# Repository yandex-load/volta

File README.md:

Yandex Volta is a framework for mobile performance and energy efficiency analysis.

[Telegram](https://t.me/joinchat/AAAAAAvBER7vU-672v1jbw) chat

**Table of Contents**

   * [Links](#links)
   * [What do you need](#what-do-you-need)
   * [Usage](#usage)
   * [Architecture](#architecture)
   * [Volta components](#volta-components)
   * [Using Volta](#using-volta)
      * [Command-line entry-point volta](#command-line-entry-point-volta)
      * [Core as module](#core-as-module)
      * [Data Providers](#data-providers)
         * [VoltaBox module](#voltabox-module)
         * [Phone module](#phone-module)
            * [Phone module - Android](#phone-module---android)
            * [Phone module - iPhone](#phone-module---iphone)
      * [Data Mappers](#data-mappers)
         * [Events module - Router](#events-module---router)
      * [Data Listeners](#data-listeners)
         * [Sync module - SyncFinder](#sync-module---syncfinder)
            * [Report module - FileListener](#report-module---filelistener)
            * [Uploader module - DataUploader](#uploader-module---datauploader)
      * [API](#api)
         * [HTTP API](#http-api)
   * [Questions](#questions)

# Links
A [mobile performance testing](https://www.youtube.com/watch?v=zcTG2PzXD3s) talk by Alexey Lavrenuke (in Russian).
An [article](https://habrahabr.ru/company/yandex/blog/311046/) about the device (in Russian).

# What do you need
* **A Volta Box**. Volta Box is an arduino-based current meter and power source for your mobile device. We will provide schematics after a while. Contact us if you want to get explanation right away.
* An **instrumented** mobile device. You need to extract a battery from your mobile device and connect **Volta Box** instead.
* If you want to control your device with **adb** while running your tests, you also need a current-limiting USB cable. Currently, we use FET to make those (google "FET current limiter").

# Usage
Install with ```pip install volta```, connect your device, run ```volta```.

# Architecture

[yEd scheme](/docs/architecture.graphml)

# Volta components
There are different types of Volta modules

[Core](volta/core/core.py) - core module, configures test life cycle and test pipeline.
Creates, configures and controls other modules.

**Data Providers**
* [VoltaBox](volta/providers/boxes/) - module for different types of Volta Boxes.
* [Phone](volta/providers/phones/) - module for different types of phones. Android and iPhone supported.

**Data Mappers**
* [Events](volta/mappers/events/) - phone logs parser module.

**Data Listeners**
* [Sync](volta/listeners/sync/) - cross-corellation sync module, syncs volta logs to phone logs.
* [Uploader](volta/listeners/uploader/) - data uploader module (e.g. to Overload).
* [Report](volta/listeners/report/) - file write module.

# Using Volta

## Command-line entry-point `volta`
Use command-line entry-point `volta` with .yaml config
> `volta -c config.yaml`

Sample yaml config for cli-wrapper:
```yaml
volta:
  enabled: true
  type: '500hz'
  source: '/dev/cu.wchusbserial1420'
phone:
  enabled: true
  type: 'android'
  source: '01e345da733a4764'
sync:
  enabled: true
  search_interval: 30
```
This config creates a test with **VoltaBox500Hz** at **/dev/cu.wchusbserial1420** and android phone id **01e345da733a4764**, then starts to collect and process data from VoltaBox and the phone.

To stop the test, press **Ctrl+C** or send **SIGTERM** signal to the process.

## Core as module
Also, if you want to control test execution or integrate Volta into your CI, you can use Core as python library.
Core validates config and reads parts with `enabled`: `True` option only.

Sample usage:
```python
from volta.core.core import Core

config = {
    'volta': {
        'enabled': True,
        'source': '/dev/cu.wchusbserial1420',
        'type': 'binary'
    },
    'phone': {
        'enabled': True,
        'source': '01e345da733a4764',
        'type': 'android',
    },
   'sync': {
       'enabled': True,
       'search_interval': 30
    },
    'uploader':{
        'enabled': True,
        'task': 'LOAD-272'
    }
}

core = Core(config)
try:
    core.configure()
    core.start_test()
except KeyboardInterrupt:
    core.end_test()
finally:
    core.post_process()
```

## Data Providers
### VoltaBox module

If you want more flexibility using Volta components, you can use provided Volta modules (or write you own) as python classes.

Available configuration options:
* **source** (mandatory) - path to volta box device
* **sample_rate** - volta box sample rate, depends on software and which type of volta box you use. Default differs for each type of VoltaBox
* **chop_ratio** - chop ratio for incoming data, describes the way how pandas.DataFrames w/ data will be created. Default 1
* **baud_rate** - baud rate for VoltaBox. Default differs for each VoltaBox class.
* **grab_timeout** - timeout for data read from VoltaBox. Default 1

Sample usage:
```python
from volta.providers.boxes.box_binary import VoltaBoxBinary
from volta.core.config.dynamic_options import DYNAMIC_OPTIONS
from netort.validated_config import ValidatedConfig as VoltaConfig
import queue
import time

config_dict = {
    'volta': {
        'source': '/dev/cu.wchusbserial1420',
        'type': 'binary'
    }
}
config = VoltaConfig(config_dict, DYNAMIC_OPTIONS, 'volta.core')
volta_box = VoltaBoxBinary(config) # VoltaBox class
q = queue.Queue()  # queue for results
volta_box.start_test(q)  # start acquiring data
time.sleep(5)  # do something (start autotests, do manual testing ...)
volta_box.end_test()  # stop acquiring data

# you can read pandas.DataFrames from results queue,
# data format: `['uts', 'value']`. Microseconds from test start and electrical currents value.
print(q.get_nowait())
```

### Phone module

We have modules for Android and iPhone. If you want to use some other type of device (e.g. Windows Phone), you can write your own phone module.

#### Phone module - Android

Works with android phones. Reads/parses system logs (`adb logcat`), starts lightning app for synchronization, installs/starts/runs tests on device.

Available configuration options:
* **source** (mandatory) - android device id
* **lightning** - path to lightning application (used for synchronization)
* **lightning_class** - lightning application class (how to run the app)
* **test_apps** - list of apps that will be installed to device for test
    * may be an url, e.g. 'http://myhost.tld/path/to/file'
    * may be a path to file, e.g. '/home/users/netort/path/to/file.apk'
* **test_class** - app class for run_test() stage
* **test_package** - app package for run_test() stage
* **test_runner** - app runner for run_test() stage

Sample usage:
```python
from volta.providers.phones.android import AndroidPhone
from volta.core.config.dynamic_options import DYNAMIC_OPTIONS
from netort.validated_config import ValidatedConfig as VoltaConfig
import queue
import time
import logging

config_dict = {
    'phone': {
        'source': '01e345da733a4764',
        'type': 'android',
        'test_apps': [
            'http://hostname.tld/path/to/first/apk1.apk',
            'http://hostname.tld/path/to/second/apk2.apk',
        ],
        'test_class': 'ru.yandex.test.highload.Tests',
        'test_package': 'ru.yandex.mobile.test',
        'test_runner': 'android.support.test.runner.AndroidJUnitRunner'
    }
}
config = VoltaConfig(config_dict, DYNAMIC_OPTIONS, 'volta.core')

phone = AndroidPhone(config)  # create Phone class
q = queue.Queue()  # create python queue for results
phone.prepare()  # prepare phone for test - clean logs, install test apps and install volta's `lightning` app for synchronization
phone.start(q)  # start acquiring log messages
phone.run_test()  # run test app, specified in config
time.sleep(5)  # do something ...
phone.end()  # stop acquiring log messages

# you can read pandas.DataFrames from results queue,
# data format: `['sys_uts', 'message']`. Microseconds from first event in phone log and message.
print(q.get_nowait())
```

#### Phone module - iPhone

Works with iPhone. Reads/parses system logs (`cfgutil`). To use this module install [Apple Configurator 2](https://itunes.apple.com/us/app/apple-configurator-2/id1037126344?mt=12) and use Mac.

To install apps on iPhone and control them you need to use `Apple's Instruments`.

Everithing else is the same as for AndroidPhone class.

Available configuration options:
* **source** (mandatory) - Apple device ECID. Run `/Applications/Apple\ Configurator\ 2.app/Contents/MacOS/cfgutil list` for getting ECID.
* **util** - path to Apple Configurator 2. Default: `/Applications/Apple\ Configurator\ 2.app/Contents/MacOS/`

Sample usage:
```python
from volta.providers.phones.iphone import iPhone
from netort.validated_config import ValidatedConfig as VoltaConfig
from volta.core.config.dynamic_options import DYNAMIC_OPTIONS

import queue

config_dict = {
    'phone': {
        'source': '0x6382910F98C26',
        'type': 'iphone',
    }
}
config = VoltaConfig(config_dict, DYNAMIC_OPTIONS, 'volta.core')
phone = iPhone(config)  # create Phone class
q = queue.Queue()  # create python queue for results
phone.prepare()  # prepare for test
phone.start(q)  # start phone log data acquiring
phone.end()  # stop phone log data acquiring
```

## Data Mappers

### Events module - Router

Once you get data from one of your phone modules, parse it with **EventsRouter**. It reads phone's results queue, parses messages, groups them by different types and sends them to listeners.

Also, applications can write any information you want into phone's system log to use later for debugging/better synchronization or mark some special events.

Available configuration options: None

Special messages format:
```
[volta] %nanotime% %type% %tag% %message%
```

Special message format sample:
```
[volta] 12345678 fragment TagFragment start
```

Currently we have those types of special messages supported by **EventsRouter**:
* **sync** - synchronization message, Sync module uses it for cross-correlation
* **event** - event message, you can write any information you need by your application on phone and send it to system log
* **fragment** - fragment message, used to mark fragments of events in your test
* **metric** - just a metric with float value instead of message.

Everything else (e.g. default phone system log messages) is grouped to **unknown** message type.

Sample usage:
```python
from volta.providers.phones.android import AndroidPhone
from volta.mappers.events.router import EventsRouter
from volta.listeners.report.report import FileListener
from volta.core.config.dynamic_options import DYNAMIC_OPTIONS
from netort.validated_config import ValidatedConfig as VoltaConfig

import queue
import time
import uuid

test_id = uuid.uuid4()  # some test id

config_dict = {
    'phone': {
        'source': '01e345da733a4764',
        'type': 'android',
    },
}
config = VoltaConfig(config_dict, DYNAMIC_OPTIONS, 'volta.core')
phone = AndroidPhone(config)  # create Phone instance
phone_q = queue.Queue()  # create python queue for results
phone.start(phone_q)  # start acquiring phone log messages

event_types = ['event', 'sync', 'fragment', 'metric', 'unknown'] # define event types
event_listeners = {key:[] for key in event_types} # create dict w/ empty list for each event type

event_fnames = {
    key:"{data}_{id}.data".format(
        data=key,
        id=test_id
    ) for key in event_types
}  # file name for each event type

# setup FileListener for each event type (at this sample we write each event type to its own file)
for type, fname in event_fnames.items():
    listener_config = {'fname': fname}
    f = FileListener(listener_config)
    event_listeners[type].append(f)

events_router = EventsRouter(phone_q, event_listeners)
events_router.start()  # start phone log messages processing and routing

time.sleep(10)
phone.end()  # stop acquiring phone log messages
time.sleep(5)
events_router.close()  # stop phone log messages processing and rouring

# in the end you will have files w/ events for each event type in current working directory
```

## Data Listeners
### Sync module - SyncFinder
Module for time synchronization. Calculates synchronization offsets for volta current measurements and phone's system log.
Uses fast Fourier transform convolution.

Available configuration options:
* **search_interval** -  sync search interval, in seconds from start. Default 30
* **sample_rate** - volta samplerate. Default 500

Sample usage:
```python
from volta.core.config.dynamic_options import DYNAMIC_OPTIONS
from volta.providers.boxes.box500hz import VoltaBox500Hz
from volta.providers.phones.android import AndroidPhone
from volta.mappers.events.router import EventsRouter
from volta.listeners.sync.sync import SyncFinder
from netort.data_processing import Tee
from netort.validated_config import ValidatedConfig as VoltaConfig

import queue
import time

# setup Volta and start
config_dict = {
    'volta': {
        'source': '/dev/cu.wchusbserial1420',
        'type': '500hz'
    },
    'phone': {
        'source': '01e345da733a4764',
        'type': 'android'
    },
    'sync': {
        'search_interval': 30
    },
}
config = VoltaConfig(config_dict, DYNAMIC_OPTIONS, 'volta.core')
volta_box = VoltaBox500Hz(config)  # create VoltaBox class
volta_q = queue.Queue()  # create python queue for volta results
volta_listeners = []  # create electrical current listeners list

# setup Phone and start
phone = AndroidPhone(config)  # create Phone class
phone_q = queue.Queue()  # create python queue for results

# setup EventsRouter
event_types = ['event', 'sync', 'fragment', 'metric', 'unknown']  # define event types
event_listeners = {key:[] for key in event_types}  # create dict w/ empty list for each event type
events_router = EventsRouter(phone_q, event_listeners)

# at the moment we have electrical currents queue and phone queue
sync_finder = SyncFinder(config)  # create SyncFinder class

# subscribe our SyncFinder to electrical current and sync events
volta_listeners.append(sync_finder)
event_listeners['sync'].append(sync_finder)

# now process electrical currents to listeners
# Tee drains the queue and send data to listeners
process_volta_data = Tee(
    volta_q,
    volta_listeners,
    'currents'
)

volta_box.start_test(volta_q)  # start volta_box data acquiring
process_volta_data.start()  # start volta_box data processing
phone.start(phone_q)  # start acquiring phone log messages
events_router.start()  # start phone logs processing and routing

# do some work... or maybe phone.run_test()
time.sleep(15)

volta_box.end_test()  # stop volta_box data acquiring
process_volta_data.close()  # stop volta_box data processing
phone.end()  # stop acquiring phone log messages
events_router.close()  # stop phone logs processing and routing

offsets = sync_finder.find_sync_points()
print(offsets)
# output format:
# sys_uts_offset is the phone's system uts to volta's uts offset
# log_uts_offset is the phone's logs custom events nanotime to volta's uts offset
# {'sys_uts_offset': -1005000, 'sync_sample': 0, 'log_uts_offset': 0}
```

#### Report module - FileListener
Saves data to a file.

Available configuration options:
* **fname** (mandatory) - Path to file.

Sample usage:
```python
from volta.providers.boxes.box500hz import VoltaBox500Hz
from volta.listeners.report.report import FileListener
from volta.core.config.dynamic_options import DYNAMIC_OPTIONS
from netort.data_processing import Tee
from netort.validated_config import ValidatedConfig as VoltaConfig
import queue
import time
import logging

config_dict = {
    'volta': {
        'source': '/dev/cu.wchusbserial1420',
        'type': '500hz'
    }
}
config = VoltaConfig(config_dict, DYNAMIC_OPTIONS, 'volta.core')
volta_box = VoltaBox500Hz(config)  # VoltaBox class
volta_q = queue.Queue()  # queue for results
volta_listeners = []  # empty list for listeners

# create FileListeners and subscribe it to volta
report_config = {'fname': 'current_output_filename'}
file_listener = FileListener(report_config)
volta_listeners.append(file_listener)

volta_data_process = Tee(volta_q, volta_listeners, 'currents')  # start volta data processing

volta_box.start_test(volta_q)  # start test and pass results queue
volta_data_process.start()
time.sleep(15) # do something (start autotests, do manual testing ...). I passed 5 seconds sleep as a placeholder.
volta_box.end_test()  # end test execution
volta_data_process.close()
```

#### Uploader module - DataUploader
Upload data. Currently supports only clickhouse TSV upload.

Available configuration options:
* **address** (mandatory) - Path to destination.
* **task** (mandatory) - You can specify task id manually.
* **test_id** - You can specify test id manually, otherwise it will be automatically generated (using uuid)

Sample yaml config section for uploader:
```yaml
uploader:
  enabled: true,
  address: 'https://lunapark.test.yandex-team.ru/api/volta'
  task: 'LOAD-272'
```

Sample usage:
```python
from volta.providers.boxes.box500hz import VoltaBox500Hz
from volta.listeners.uploader.uploader import DataUploader
from volta.core.config.dynamic_options import DYNAMIC_OPTIONS
from netort.data_processing import Tee
from netort.validated_config import ValidatedConfig as VoltaConfig
import queue
import time
import logging

config_dict = {
    'volta': {
        'source': '/dev/cu.wchusbserial1420',
        'type': '500hz'
    },
    'uploader': {
        'task': 'LOAD-272'
    }
}
config = VoltaConfig(config_dict, DYNAMIC_OPTIONS, 'volta.core')
volta_box = VoltaBox500Hz(config)  # VoltaBox class
volta_q = queue.Queue()  # queue for results
volta_listeners = []  # emptry list for listeners

# create DataUploader and subscribe it to volta_box
uploader = DataUploader(config)
volta_listeners.append(uploader)

volta_data_process = Tee(volta_q, volta_listeners, 'currents')  # start volta data processing

volta_box.start_test(volta_q)  # start test and pass results queue
volta_data_process.start()
time.sleep(15) # do something (start autotests, do manual testing ...). I passed 5 seconds sleep as a placeholder.
volta_box.end_test()  # end test execution
volta_data_process.close()
```

## API
### HTTP API (concurrent tests, improved statuses)
Allows to start and stop test via HTTP interface.

Entry point: `volta-api`

Simply put config into a POST body.

Start test sample:
```bash
curl 'http://localhost:9998/api/v1/start/' --data 'config={"volta":{"source":"/dev/cu.wchusbserial1420","type":"500hz","enabled":True}, "uploader": {"enabled": True, "task":"LOAD-272"},"phone":{"source":"1f434a75","type":"android","enabled":True}}' -v
```

Stop test sample:
```bash
curl 'http://localhost:9998/api/v1/stop?session=20170801180806_0000000000'
```

Check test status:
```bash
curl 'http://localhost:9998/api/v1/status?session=20170801180806_0000000000'
```

### simple and mini HTTP API (no concurrent tests allowed)
Allows to start and stop test via HTTP interface.

Entry point: `volta-http`

Simply put config into a POST body.

Start test sample:
```bash
curl 'http://localhost:9998/api/v1/start/' --data 'config={"volta":{"source":"/dev/cu.wchusbserial1420","type":"500hz","enabled":True}}' -v
```

Stop test sample:
```bash
curl 'http://localhost:9998/api/v1/stop/' -XPOST -v
```

# Questions
Any questions to Alexey Lavrenuke <direvius@yandex-team.ru> OR [Telegram](https://t.me/joinchat/AAAAAAvBER7vU-672v1jbw) chat.

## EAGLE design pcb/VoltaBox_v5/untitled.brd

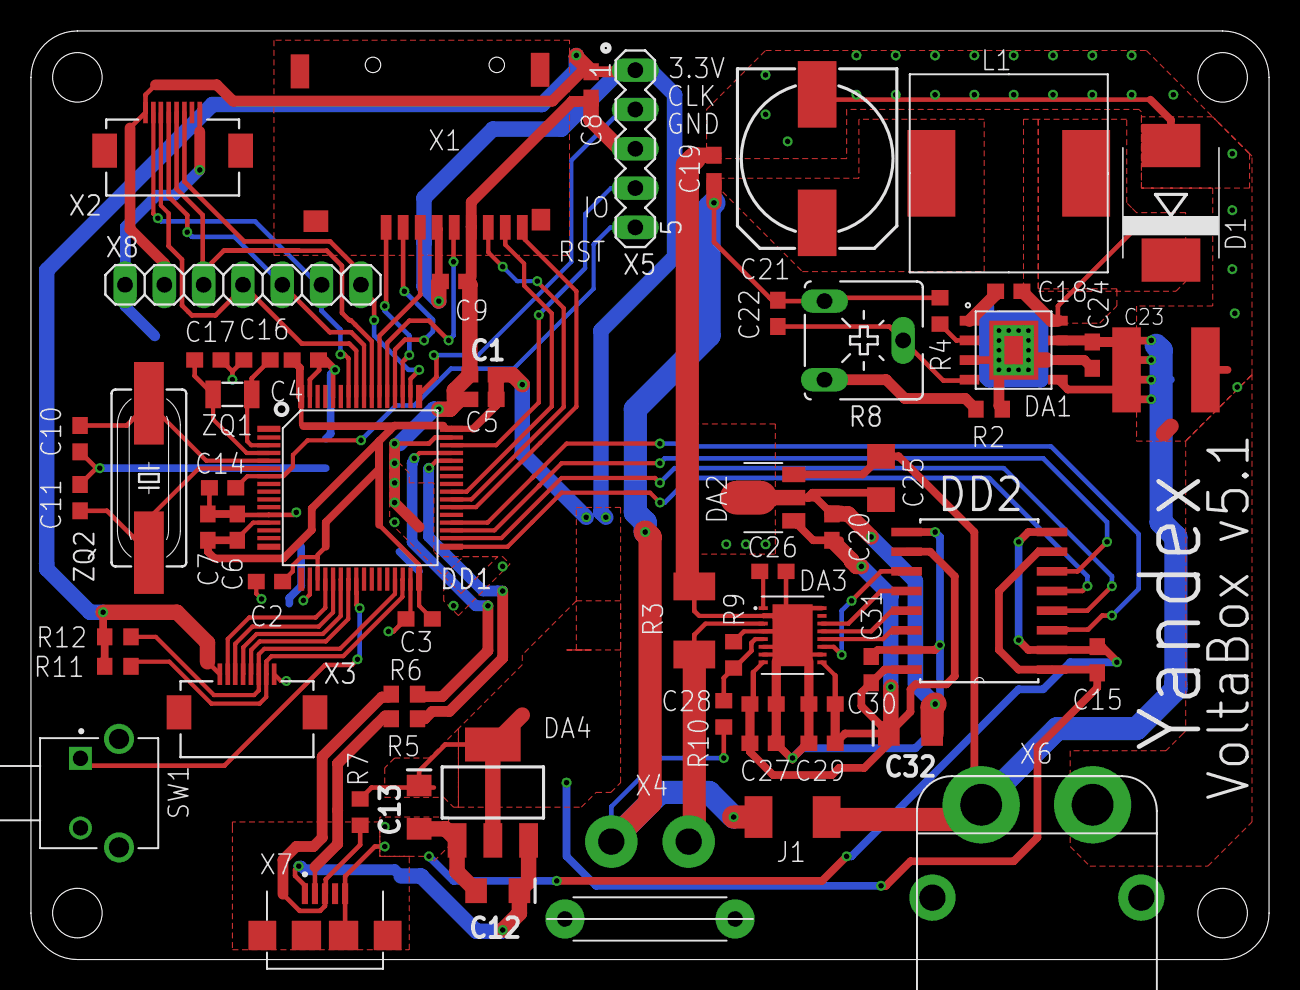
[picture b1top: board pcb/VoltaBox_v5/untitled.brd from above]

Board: 2 copper layers, 80.0 x 60.0 mm, 63 parts (0 on the bottom side), 53 nets.

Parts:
C1: 4.7uF; 0603
C2, C3, C4, C5, C14, C15, C18, C19, C20, C24, C28, C29, C31: 0.1u; C0603
C6, C8, C9, C26: 1u; C0603
C7: 10n; C0603
C10, C11, C16, C17: 15p; C0603
C12, C13, C32: 10uF; EIA3216
C21: 100u; 150CLZ-1014
C22: 150p; C0603
C23: 4.7u; C2220K
C25: 1u; C1206
C27, C30: 10p; C0603
D1: STPS5L60S; SMC
DA1: ST1S14; HSOP8
DA2: 78L05F; SOT89
DA3: LMP92064SD/NOPB; SON50P400X500X80-17N
DA4: SOT223
DD1: MCU-STM32F103RCT6(LQFP64); LQFP64-0.5-10X10MM
DD2: ADUM1401CRWZ; SO-16W
J1: 0; R2010
L1: B82477G4
R2, R10: 2.7K; R0603
R3: 0.025; R2010
R4: 47K; R0603
R5, R6: 22; R0603
R7: 1.5k; R0603
R8: 10k; CA6V
R9: 1.2K; R0603
R11, R12: 10k; R0603
SW1: FSMRA6JH; TE_FSMRA6JH
X1: 112J-TDAR-R(MICROSD); 112J-TDAR-R
X2, X3: 52892-0895; MOLEX_52892-0895
X4: XT30PW-F
X5: MA05-1
X6: XT60PW-M
X7: KLS1-233
X8: 1X07
ZQ1: 32768Hz; 3.2X1.5
ZQ2: 8MHz; HC49UP

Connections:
+3V3: C1.1, C2.1, C3.1, C4.1, C5.1, C6.1, C7.1, C8.1, C9.1, C13.+, C15.1, DA4.2, DA4.4, DD1.13, DD1.19, DD1.32, DD1.48, DD1.64, DD2.1, DD2.7, R7.2, R11.2, R12.2, X1.P$4, X2.1, X3.1, X5.1, X8.2
+4V: C19.1, C21.+, C22.2, J1.2, L1.P$2, R4.2, R8.A, R10.2, X4.P$2
+5V: C20.1, C27.1, C28.1, C29.1, C30.1, C31.1, C32.+, DA2.1, DA3.8, DA3.9, DD2.10, DD2.16
+12V: C23.1, C24.1, C25.1, DA1.5, DA1.7, DA2.3, J1.1, X6.P$2
ADC_MISO: DD1.35, DD2.6
ADC_MOSI: DD1.36, DD2.3
ADC_NSS: DD1.33, DD2.5
ADC_SCK: DD1.34, DD2.4
AGND: C19.2, C20.2, C21.-, C23.2, C24.2, C25.2, C26.2, C27.2, C28.2, C29.2, C30.2, C31.2, C32.-, D1.A, DA1.3, DA1.6, DA1.P$9, DA1.P$10, DA1.P$11, DA1.P$12, DA1.P$13, DA1.P$14, DA1.P$15, DA1.P$16, DA1.P$17, DA1.P$18, DA1.P$19, DA1.P$20, DA1.P$21, DA1.P$22, DA2.2, DA2.2@1, DA3.2, DA3.4, DA3.6, DA3.7, DA3.10, DA3.16, DA3.17, DD2.9, DD2.15, R2.1, R3.1, R9.1, X6.P$1
DMCU_N: DD1.44, R5.2
DMCU_P: DD1.45, R6.2
D_N: R5.1, X7.2
D_P: R6.1, R7.1, X7.3
GND: C1.2, C2.2, C3.2, C4.2, C5.2, C6.2, C7.2, C8.2, C9.2, C10.2, C11.2, C12.-, C13.-, C14.2, C15.2, C16.2, C17.2, DA4.1, DD1.12, DD1.18, DD1.31, DD1.47, DD1.60, DD1.63, DD2.2, DD2.8, SW1.2, SW1.S1, SW1.S2, X1.P$6, X1.P$10, X1.P$11, X1.P$12, X1.P$13, X2.8, X3.8, X5.3, X7.5, X7.SH4, X7.SH5, X7.SH6, X7.SH7, X8.1
unnamed: C10.1, DD1.5, ZQ2.1
unnamed: C11.1, DD1.6, ZQ2.2
unnamed: C26.1, DA3.1
unnamed: C18.1, DA1.1
unnamed: DA3.13, DD2.13
unnamed: DA3.14, DD2.12
unnamed: C17.1, DD1.4, ZQ1.2
unnamed: C16.1, DD1.3, ZQ1.1
unnamed: C18.2, D1.C, DA1.8, L1.P$1
unnamed: C22.1, DA1.4, R8.S
unnamed: DA3.12, DD2.14
unnamed: DA1.2, R4.1
unnamed: DD1.54, X1.P$3
unnamed: DD1.53, X1.P$5
unnamed: DD1.52, X1.P$2
unnamed: DD1.51, X1.P$1
unnamed: DD1.24, SW1.1
unnamed: DD1.40, X1.P$8
unnamed: DD1.39, X1.P$7
unnamed: R2.2, R8.E
unnamed: DA3.3, R3.2, X4.P$1
unnamed: DD1.30, R11.1, X3.7
unnamed: DA3.5, R9.2, R10.1
unnamed: DA3.11, DD2.11
unnamed: DD1.29, R12.1, X3.6
unnamed: DD1.23, X3.5
unnamed: DD1.22, X3.4
unnamed: DD1.21, X3.3
unnamed: DD1.20, X3.2
unnamed: DD1.38, X1.P$9
NRESET: C14.1, DD1.7, X5.5
OLED_CS: DD1.50, X2.6, X8.7
OLED_DC: DD1.58, X2.2, X8.6
OLED_MOSI: DD1.57, X2.3, X8.4
OLED_RS: DD1.56, X2.4, X8.5
OLED_SCK: DD1.55, X2.5, X8.3
SWCLK: DD1.49, X5.2
SWDIO: DD1.46, X5.4
VCC: C12.+, DA4.3, X7.1

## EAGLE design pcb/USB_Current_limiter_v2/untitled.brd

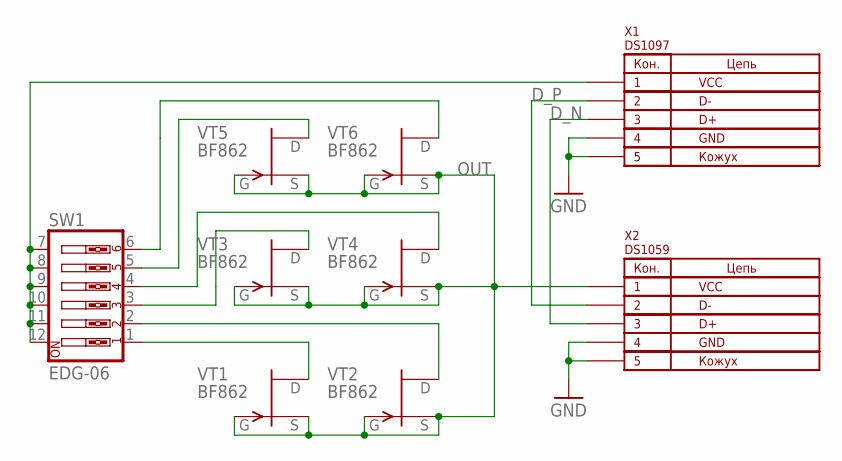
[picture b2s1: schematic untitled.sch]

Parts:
SW1: EDG-06
VT1, VT2, VT3, VT4, VT5, VT6: BF862; SOT23
X1: DS1097
X2: DS1059

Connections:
D_N: X1.P$2, X2.P$3
D_P: X1.P$3, X2.P$2
GND: X1.P$1, X1.P$5, X1.P$6, X2.P$4, X2.P$5, X2.P$6
unnamed: SW1.6, VT6.2 (D)
unnamed: SW1.7, SW1.8, SW1.9, SW1.10, SW1.11, SW1.12, X1.P$4
unnamed: SW1.5, VT5.2 (D)
unnamed: SW1.4, VT4.2 (D)
unnamed: SW1.3, VT3.2 (D)
unnamed: SW1.2, VT2.2 (D)
unnamed: SW1.1, VT1.2 (D)
OUT: VT1.1 (S), VT1.3 (G), VT2.1 (S), VT2.3 (G), VT3.1 (S), VT3.3 (G), VT4.1 (S), VT4.3 (G), VT5.1 (S), VT5.3 (G), VT6.1 (S), VT6.3 (G), X2.P$1

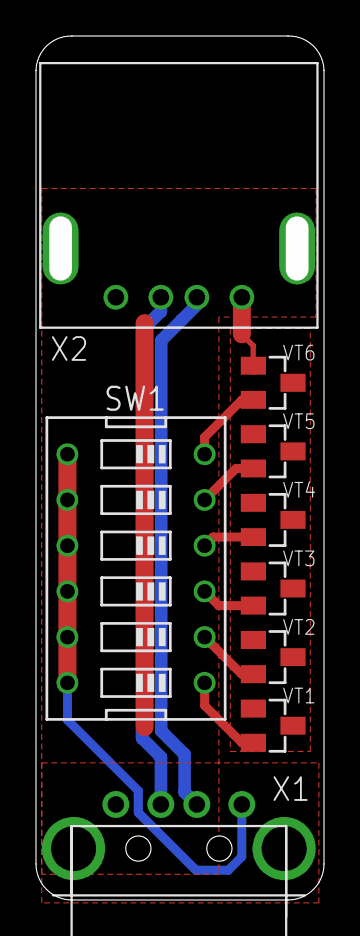
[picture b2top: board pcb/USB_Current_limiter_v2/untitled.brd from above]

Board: 2 copper layers, 16.0 x 48.0 mm, 9 parts (0 on the bottom side), 11 nets.

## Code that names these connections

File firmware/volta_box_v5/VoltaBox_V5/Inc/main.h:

/**
  ******************************************************************************
  * @file           : main.h
  * @brief          : Header for main.c file.
  *                   This file contains the common defines of the application.
  ******************************************************************************
  * This notice applies to any and all portions of this file
  * that are not between comment pairs USER CODE BEGIN and
  * USER CODE END. Other portions of this file, whether 
  * inserted by the user or by software development tools
  * are owned by their respective copyright owners.
  *
  * Copyright (c) 2018 STMicroelectronics International N.V. 
  * All rights reserved.
  *
  * Redistribution and use in source and binary forms, with or without 
  * modification, are permitted, provided that the following conditions are met:
  *
  * 1. Redistribution of source code must retain the above copyright notice, 
  *    this list of conditions and the following disclaimer.
  * 2. Redistributions in binary form must reproduce the above copyright notice,
  *    this list of conditions and the following disclaimer in the documentation
  *    and/or other materials provided with the distribution.
  * 3. Neither the name of STMicroelectronics nor the names of other 
  *    contributors to this software may be used to endorse or promote products 
  *    derived from this software without specific written permission.
  * 4. This software, including modifications and/or derivative works of this 
  *    software, must execute solely and exclusively on microcontroller or
  *    microprocessor devices manufactured by or for STMicroelectronics.
  * 5. Redistribution and use of this software other than as permitted under 
  *    this license is void and will automatically terminate your rights under 
  *    this license. 
  *
  * THIS SOFTWARE IS PROVIDED BY STMICROELECTRONICS AND CONTRIBUTORS "AS IS" 
  * AND ANY EXPRESS, IMPLIED OR STATUTORY WARRANTIES, INCLUDING, BUT NOT 
  * LIMITED TO, THE IMPLIED WARRANTIES OF MERCHANTABILITY, FITNESS FOR A 
  * PARTICULAR PURPOSE AND NON-INFRINGEMENT OF THIRD PARTY INTELLECTUAL PROPERTY
  * RIGHTS ARE DISCLAIMED TO THE FULLEST EXTENT PERMITTED BY LAW. IN NO EVENT 
  * SHALL STMICROELECTRONICS OR CONTRIBUTORS BE LIABLE FOR ANY DIRECT, INDIRECT,
  * INCIDENTAL, SPECIAL, EXEMPLARY, OR CONSEQUENTIAL DAMAGES (INCLUDING, BUT NOT
  * LIMITED TO, PROCUREMENT OF SUBSTITUTE GOODS OR SERVICES; LOSS OF USE, DATA, 
  * OR PROFITS; OR BUSINESS INTERRUPTION) HOWEVER CAUSED AND ON ANY THEORY OF 
  * LIABILITY, WHETHER IN CONTRACT, STRICT LIABILITY, OR TORT (INCLUDING 
  * NEGLIGENCE OR OTHERWISE) ARISING IN ANY WAY OUT OF THE USE OF THIS SOFTWARE,
  * EVEN IF ADVISED OF THE POSSIBILITY OF SUCH DAMAGE.
  *
  ******************************************************************************
  */

/* Define to prevent recursive inclusion -------------------------------------*/
#ifndef __MAIN_H__
#define __MAIN_H__

/* Includes ------------------------------------------------------------------*/

/* USER CODE BEGIN Includes */

/* USER CODE END Includes */

/* Private define ------------------------------------------------------------*/

#define SPI2_NSS_Pin GPIO_PIN_12
#define SPI2_NSS_GPIO_Port GPIOB
#define OLED_CS_Pin GPIO_PIN_15
#define OLED_CS_GPIO_Port GPIOA
#define OLED_SCK_Pin GPIO_PIN_3
#define OLED_SCK_GPIO_Port GPIOB
#define OLED_RS_Pin GPIO_PIN_4
#define OLED_RS_GPIO_Port GPIOB
#define OLED_MOSI_Pin GPIO_PIN_5
#define OLED_MOSI_GPIO_Port GPIOB
#define OLED_DC_Pin GPIO_PIN_6
#define OLED_DC_GPIO_Port GPIOB

/* ########################## Assert Selection ############################## */
/**
  * @brief Uncomment the line below to expanse the "assert_param" macro in the 
  *        HAL drivers code
  */
/* #define USE_FULL_ASSERT    1U */

/* USER CODE BEGIN Private defines */

/* USER CODE END Private defines */

#ifdef __cplusplus
 extern "C" {
#endif
void _Error_Handler(char *, int);

#define Error_Handler() _Error_Handler(__FILE__, __LINE__)
#ifdef __cplusplus
}
#endif

#endif /* __MAIN_H__ */

/************************ (C) COPYRIGHT STMicroelectronics *****END OF FILE****/

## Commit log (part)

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2017-02-16 reinit SD card every time
2017-02-17 fix led brightness
2017-02-17 verify=False everywhere
2017-02-17 version bump
2017-03-01 added task for console wiazrd
2017-03-01 task id for uploader, version bump
2017-03-01 fixes, raw data from sd-card uploader ignores meta info
2017-03-03 Added under construction css for wizard when test started
2017-03-05 added 1MHz and esp8266 firmwares
2017-03-06 20 seconds flashlight sync now
2017-03-06 added local graphs
2017-03-06 removed pngs
2017-03-06 local plots
2017-03-06 lunapark task checker added
2017-03-06 add test fragments parsing, need to complete uploading
2017-03-07 added exception failover if user forgot to connect the box
2017-03-07 bugfixes
2017-03-12 bugfix
2017-03-14 4digit display support added
2017-03-17 filter trash and fill w/ zeroes while grabbing plain-text data
2017-03-20 jobno dump, version bump
2017-03-21 interrupts handler
2017-03-21 added env variables, added log events and fragments cosmetics
2017-03-21 added operator login to wizard ui
2017-03-22 removed pyqt and version bump
2017-03-22 bugfix, rollback of fragments. falsestart
2017-03-22 ver bump
2017-03-23 made uploader more stable if events not found
2017-03-23 appropriate logic for operator detection
2017-03-27 VoltaBox refactoring init
2017-03-28 VoltaBox refactoring
2017-03-28 architecture image, cosmetics
2017-03-28 VoltaBox binary refactoring
2017-03-28 TimeChopper moved to util, odd serial read workaround added -> orphan byte superstar
2017-03-28 cosmetics
2017-03-30 appropriate end for reader, file import mode for binary
2017-04-03 added resource manager, refactored volta boxes to work w/ resource manager
2017-04-05 Phone interface, android blank step implementation
2017-04-05 moved lightning to Phones, added resource manager to android
2017-04-05 usage sample fix
2017-04-05 install lightning apk
2017-04-07 android phone refactoring, 10khz filereader to dataframe bugfix
2017-04-07 cleanup
2017-04-10 wizard fixes, no connection to lunapark
2017-04-10 ui fixes
2017-04-11 Phones->android refactoring
2017-04-11 phone.run_test added to core
2017-04-12 more human-friendly cosmetics patch for android
2017-04-12 ver bumpg
2017-04-12 type fix
2017-04-12 todo added to android phone
2017-04-12 meta.duration removed
2017-04-12 cosmetics, code cleanup
2017-04-13 Phones -> iPhone refactoring init
2017-04-13 iphone and android timestamps to datetime
2017-04-13 code cleanup
2017-04-17 eventshandler init
2017-04-17 more flexible data usage in eventsparser
2017-04-17 regexp fixes
2017-04-17 removed redundant ? in regexp
2017-04-18 added ts to volta dataframes
2017-04-18 daterange for volta currents
2017-04-18 time.time -> utc
2017-04-18 start_time from test start
2017-05-05 sync finder init
2017-05-05 removed junk
2017-05-15 everything moved to async/threads, FileListener init, Sync reworked, Tee init
2017-05-16 file listeners refactoring, added header to filelisteners, separate file listeners for each event types
2017-05-17 uploader init
2017-05-17 cli init, yaml config parser and sample
2017-05-18 json/yaml support, failover cli config added
2017-05-19 readme bugfix
2017-05-19 Added scheme png
2017-05-19 readme fix
2017-05-22 Listeners refactoring, added interfaces and docstrings
2017-05-22 docstrings for core
2017-05-22 docstring redesign, LogReader for Phone refactoring
2017-05-22 moved to develop
2017-05-22 PEP8 naming for modules
2017-05-23 bugfix for android volta.Phones -> phones
2017-05-23 postloader init
2017-05-23 gitignore mac junk removal
2017-05-23 moved Boxes according to PEP8 module naming
2017-05-23 PEP8 module naming
2017-05-23 cleanup, removed junk
2017-05-24 Update README.md
    lil fixies
2017-05-25 reorganization eventsrouter
2017-05-25 events router documentation
2017-05-25 Sync class documentation
2017-05-25 relative links to modules
2017-05-25 readme update
2017-05-25 FileListener documentation
2017-05-26 added datauploader sampe and documentation
2017-05-26 typo fix
2017-05-26 Table of Contents
2017-05-29 package reorganization - group by type
2017-05-29 modules reorganization - update, readme update
2017-05-29 ToC update
2017-05-30 add Volta image
2017-05-30 update photo
2017-05-30 uploader meta upload, config samples
2017-05-30 uploader meta create and update job
2017-05-30 readme samples update
2017-05-30 key_date added to start of test_id
2017-06-01 http api v1
2017-06-01 more flexible error handling for api
2017-06-01 Readme for http api
2017-06-07 ToC update, API documentation
2017-06-07 uploader config readme fix
2017-06-17 add telegram chat link
2017-06-19 add demo ipynb
2017-06-22 uploader bug fix, added logging for sync stage
2017-06-22 Sync w/ master
2017-06-26 added sample configs, nexus4 phone, additional logging
2017-06-27 remove exceptional logging
2017-06-28 eventsrouter bugfix if message is empty
2017-06-28 removed infinite loop for phone events processing
2017-06-29 added lunapark id
2017-07-04 hotfix if row.message in router is empty
2017-07-12 added deps versions
2017-07-12 slope and offset for binary box
2017-07-17 custom regexp support
2017-07-20 android below 5 class
2017-07-20 old android phones core support
2017-07-20 validation for configuration system, refactoring
2017-07-20 android old refactoring
2017-07-20 samples updated
2017-07-21 documentation update for validator
2017-07-21 documentation update
2017-07-24 improvements for tank android plugin
2017-07-24 added event_regexp for validation schema.yaml
2017-07-24 removed unplug_type=manual
2017-07-26 volta core config update
2017-07-26 volta get test id handler added
2017-07-26 jobno, api_jobno renamed
2017-07-27 current test info method
2017-07-31 new webserver for API
2017-07-31 added future to deps
2017-07-31 manager, webserver and worker for API
2017-07-31 added readme and samples
2017-07-31 common cleanup
2017-07-31 appropriate artifacts handling and initialization
2017-08-01 api improvements, phone code cleanup
2017-08-01 Readme update, cosmetics
2017-08-02 binary apk bugfix
2017-08-02 bugfix of binary apk distribution
2017-08-02 revert back apk from MANIFEST
2017-08-14 device_id for tests
2017-08-17 iphone config bugfix
2017-08-17 bugfix again, version bump
2017-08-18 fix router if dataframe is None
2017-08-23 add firmware for ads7816 based VoltaBox
2017-08-25 removed sleeps for start test
2017-08-29 volta w/external ads
2017-08-29 version
2017-09-04 iphone bugfix
2017-09-15 removed infinite loop from iphone
2017-10-02 pcb schemas added
2017-10-09 ratatoskr@ patch
2017-10-09 sleep till flashlight app ends its work
2017-10-12 cleanup apps VOLTA-238
2017-10-12 cleanup bufixes
2017-10-20 stm32+ads7816 firmware boilerplate
2017-10-31 events router exceptions: trying to be more stable to bad events
2017-11-02 bug fix for log_uts_offset
2017-11-23 volta box v4
2017-11-24 Require 'enabled' option for volta module
2017-11-24 bugfix for events processing
2017-11-28 tutorial update
2017-11-30 VoltaBox v4 PCB
2017-11-30 update pcb
2017-12-07 added note about ECID for iOS
2017-12-07 fix some bugs
2017-12-18 uploader async w/ threading. refactoring uploader listener
2017-12-18 chop ratio validation fixes
2017-12-18 added retry for uploader
2017-12-19 additional exception for jobno dump, cosmetics
2017-12-19 send chunk method
2017-12-19 more suitable warning message for retry
2017-12-19 added test info for volta API for uploader sender thread
2017-12-26 get-state failover
2017-12-26 Ver bump|
2017-12-28 new schematics
2018-01-11 fixed bugs for threads, uploader thread refactoring and reorganization
2018-01-16 restore orphan byte
2018-01-16 revert back regress id, added daemons for threading Drain/Tee
2018-01-16 events router improvements, additional logging for events router and uploader
2018-01-16 uploader and android phone test performer improvements
2018-01-17 sample swap configuration
2018-01-19 Regress -> component
2018-01-23 uploader should now correctly finish its work
2018-01-26 empty dataframes skip for uploader
2018-01-29 new logging system and management, volta log added to artifacts
2018-02-01 exceptions for uploader, create_job and update_job timeouts and connection errors catch
2018-02-01 ver bump, bugfix
2018-02-21 new pcb
2018-02-21 ran python-modernize
2018-02-22 moved common utils to netort
2018-03-05 hardcoded port removed for http api
2018-03-07 readme and setup update
2018-03-07 requirements update
2018-03-07 post-loader improvements
2018-03-07 uploader updated to validator config
2018-03-07 uploader bugfixes, code cleanup
2018-03-07 added version to logs, added exception catch for bad voltabox initialization
2018-03-07 exception catch for bad volta initialization
2018-03-12 sync points exception catch, ver bump
2018-03-12 meta data fix for volta-uploader
2018-03-12 appropriate retrying for uploader, ver bump
2018-03-13 retrying refactoring, threads closing refactoring, ver bump
2018-03-13 bugfix logger
2018-03-13 logger bugfixes
2018-04-27 fix test script
2018-06-01 removed old router
2018-06-06 refactored events and iphone provider
2018-06-19 android provider, console, sync adopted to data_session
2018-07-11 adb start-server added for android phones
2018-07-16 patches added to cli
2018-07-19 removed errors checks for android adb execution due to false-positive failures
2018-07-19 retrying for core test finish
2018-07-23 volta box v5 read values from adc
2018-07-23 added default configs for volta, /etc/volta.yaml
2018-07-23 send data over usb cdc
2018-08-07 New analog part with BluePill firmware; update HAL (fixes usb bugs for MacOS)
2018-08-07 use stlink v2.1 config
2018-08-08 fix timer
2018-08-20 test for multiple open-read-close cycle
    Written by direvius@ this script performs multiple readings.
    Success: script reads data and prints output
    Fail: script hangs indefinitely
2018-09-19 warn is deprecated. using warning;
2018-09-20 cleanup;
2018-09-20 don't wait for daemon threads;
2018-09-21 fix offset updating;
2018-09-24 var bump;
2018-09-24 setting metric offsets in luna;
2018-10-02 VoltaBox_v5 pcb initial commit
2018-10-03 Some PCB changes. ICs prefix changes. Added some capacitors. Q3 case type changed.
2018-10-04 DC-DC new layout, adc part implemented
2018-10-05 micro usb to usb-b, dc-dc inductor replaced, some schematic changes
2018-10-09 Some pcb changes, dc-dc capacitors replaced.
2018-10-10 usb route done, some pcb and schematic changes, added power connectors, dc-dc diode replaced, added TODO file
2018-10-11 pcb adaptation for existing case
2018-10-12 pre final
2018-10-13 Changed all GND nets in dc-dc and adc part to AGND. Changed usb footprint to correct usb footprint (kls1-233-1-x-x to kls1-233-0-x-x (it's doesn't need holes in pcb that must be very close to the con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
2018-10-13 Relocated all silk labels to it's places. Renamed isolator's model. Added some text to the top silk (tPlace).
2018-10-15 PCB mount holes drill change 3 -> 3.2
2018-10-15 polygon under adc added
2018-10-15 microsdcard holder footprint edit
2018-10-16 new current limiter
2018-10-26 netort version bump;
2018-11-01 oversampling x4 implemented
2018-11-08 usb fixed
2018-11-08 time_limit option;
2018-11-08 mcu freq 48MHz->72MHz, gpio speed optimization
2018-11-09 reading 4 samples every 0.1ms, 10khz interrupts
2018-11-14 revert time_limit option;
2018-11-14 Base firmware for vb5 board added
2018-12-13 2to3
2018-12-13 ver bump;
2018-12-17 dealing with bytes/str issues;
2018-12-20 ignore future warinings;
2018-12-24 use new balancer;
2018-12-24 python_requires='>=3';
2018-12-24 correct import;
2019-02-13 netort returns bytes, which are treated as str
    get_nowait_from_queue returns bytes.
    chunk.strip('\n') fails then with error 'TypeError: a bytes-like object is required, not 'str''
2019-02-14 fix for LUNA-314
2019-02-15 simplified strip() (as in AndroidPhone)
2019-02-26 VB5 DC-DC GND fixed, STM32 boot pin connected
2019-05-21 additional oled connector added, some small fixes, swd relayout
2019-06-10 upd to new netort
2019-06-10 upd to new netort 2
2019-07-03 v0.7.3: netort==0.3.4
2019-08-06 rtc disabled; build fixed
2019-08-06 removed some trash from src dir
2019-08-06 removed some trash from src dir2

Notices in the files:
parts and their libraries:
SparkFun-Capacitors: Licensing: Creative Commons ShareAlike 4.0 International - https://creativecommons.org/licenses/by-sa/4.0
crystal-geyer_V1_0: Copyright: Geyer-Electronic
